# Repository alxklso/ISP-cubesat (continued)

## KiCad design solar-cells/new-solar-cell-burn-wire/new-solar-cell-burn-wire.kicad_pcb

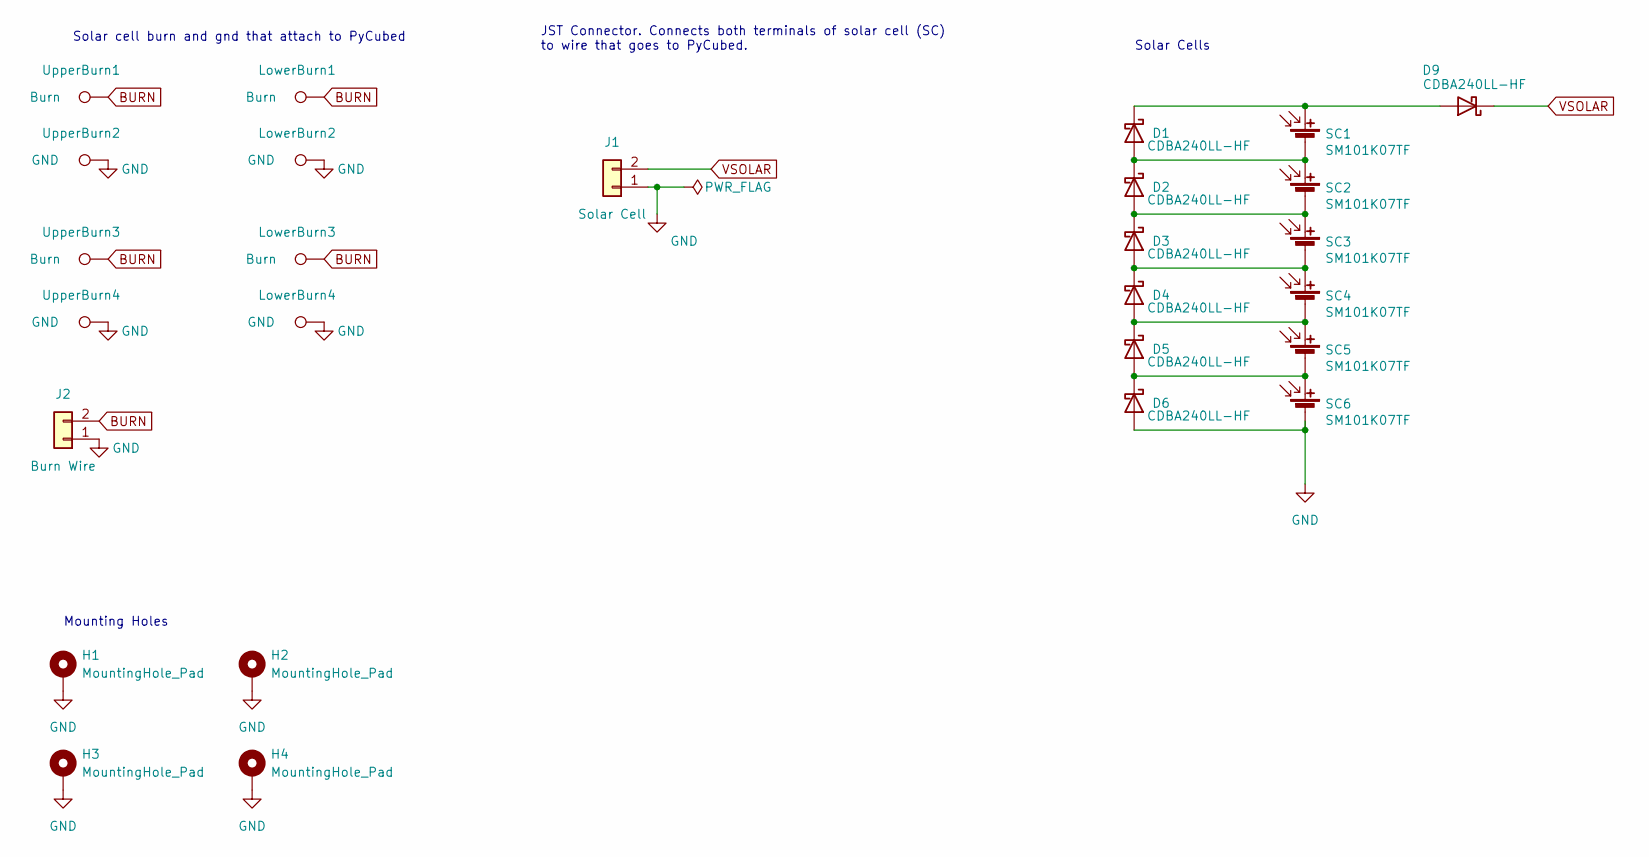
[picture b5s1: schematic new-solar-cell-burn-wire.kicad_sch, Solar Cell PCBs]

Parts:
D1, D2, D3, D4, D5, D6, D9: CDBA240LL-HF; DO-214AC
H1, H2, H3, H4: MountingHole_Pad; MountingHole_3.2mm_M3_DIN965_Pad
J1: Solar Cell; 2053380002
J2: Burn Wire; 2053380002
LowerBurn1, LowerBurn3: Burn; TestPoint_THTPad_2.0x2.0mm_Drill1.0mm
LowerBurn2, LowerBurn4: GND; TestPoint_THTPad_2.0x2.0mm_Drill1.0mm
SC1, SC2, SC3, SC4, SC5, SC6: SM101K07TF
UpperBurn1, UpperBurn3: Burn; TestPoint_THTPad_2.0x2.0mm_Drill1.0mm
UpperBurn2, UpperBurn4: GND; TestPoint_THTPad_2.0x2.0mm_Drill1.0mm

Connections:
BURN: J2.2, LowerBurn1.1, LowerBurn3.1, UpperBurn1.1, UpperBurn3.1
GND: D6.2 (A), H1.1, H2.1, H3.1, H4.1, J1.1, J2.1, LowerBurn2.1, LowerBurn4.1, SC6.2 (-), UpperBurn2.1, UpperBurn4.1; also elsewhere on the board
unnamed: D1.1 (K), D9.2 (A), SC1.1 (+)
unnamed: D1.2 (A), D2.1 (K), SC1.2 (-), SC2.1 (+)
unnamed: D2.2 (A), D3.1 (K), SC2.2 (-), SC3.1 (+)
unnamed: D3.2 (A), D4.1 (K), SC3.2 (-), SC4.1 (+)
unnamed: D4.2 (A), D5.1 (K), SC4.2 (-), SC5.1 (+)
unnamed: D5.2 (A), D6.1 (K), SC5.2 (-), SC6.1 (+)
VSOLAR: D9.1 (K), J1.2; also elsewhere on the board

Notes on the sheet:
Solar cell burn and gnd that attach to PyCubed
Mounting Holes
Solar Cells
JST Connector. Connects both terminals of solar cell (SC) to wire that goes to PyCubed.

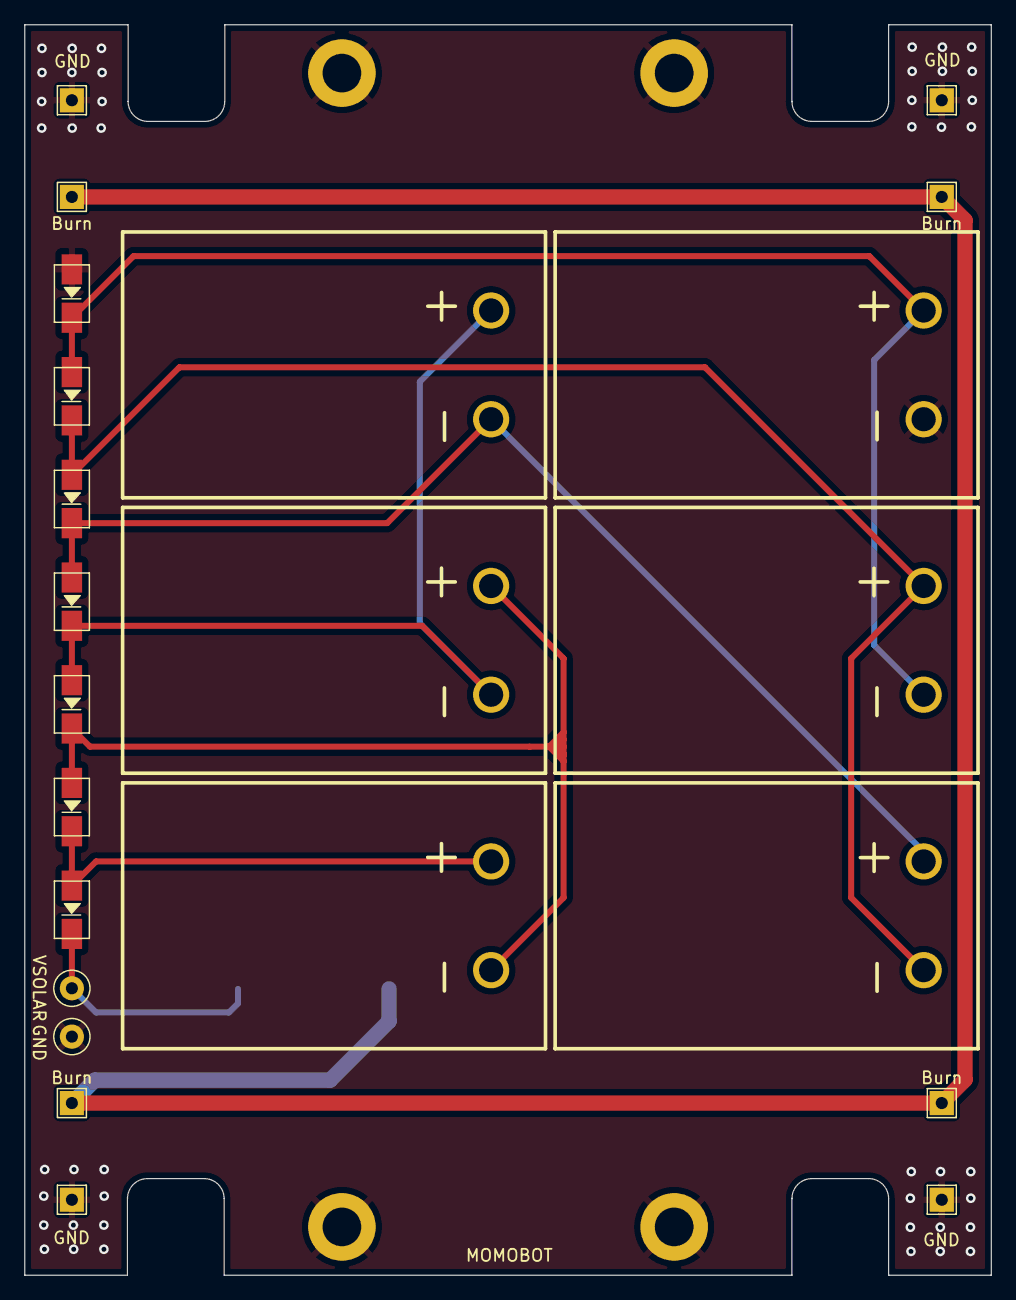
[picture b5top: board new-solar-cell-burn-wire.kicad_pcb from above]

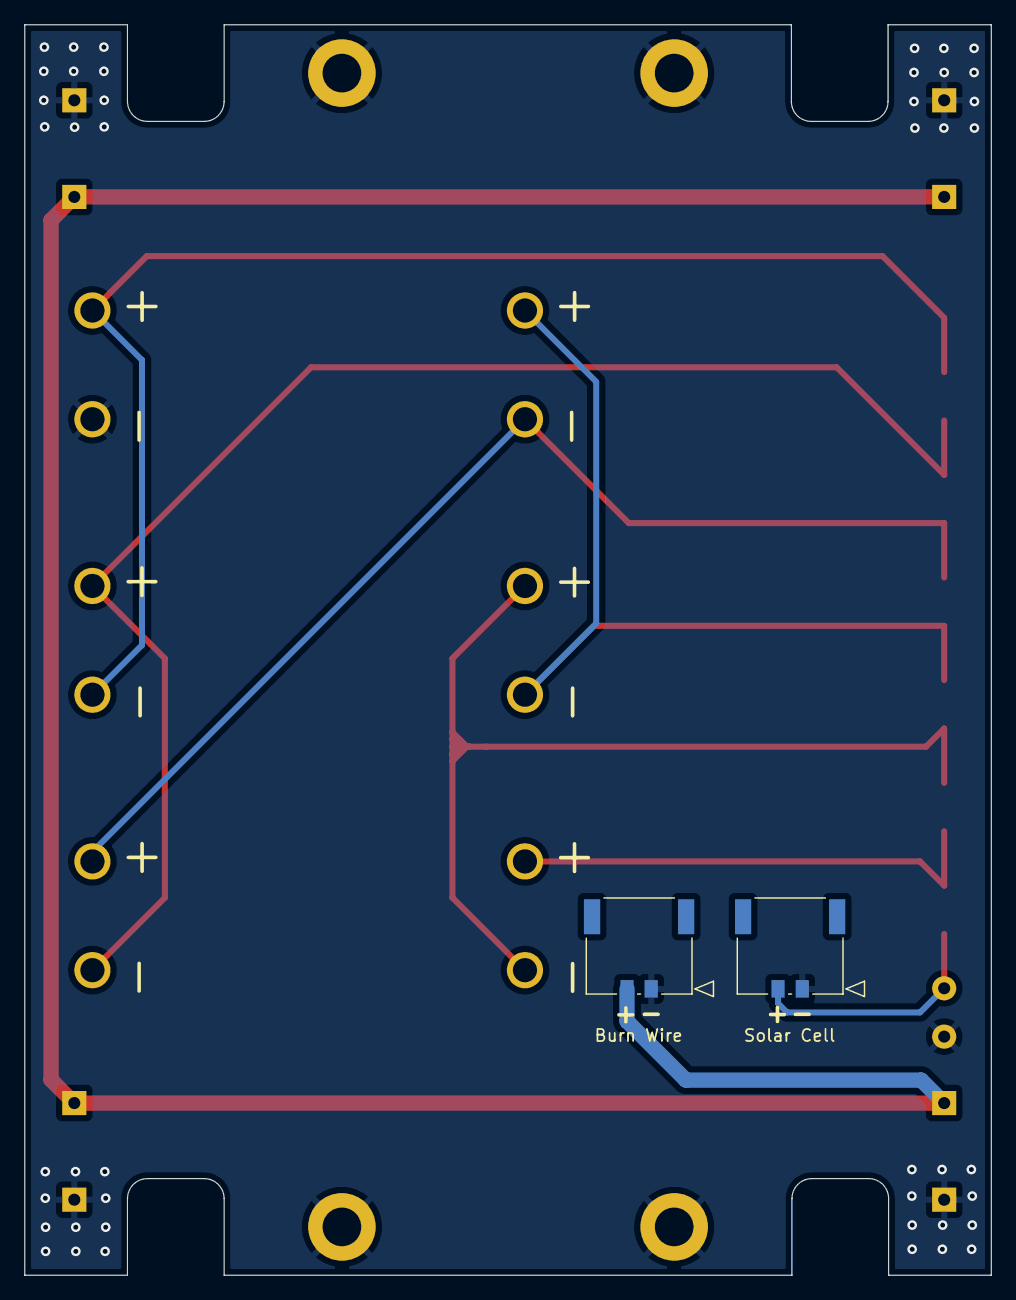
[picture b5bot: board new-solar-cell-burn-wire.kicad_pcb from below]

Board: 2 copper layers, 80.0 x 103.5 mm, 29 parts (2 on the bottom side), 9 nets.

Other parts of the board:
TP1: VSOLAR; TestPoint_Loop_D1.80mm_Drill1.0mm_Beaded
TP2: GND; TestPoint_Loop_D1.80mm_Drill1.0mm_Beaded

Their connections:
GND: TP2.1; also elsewhere on the board
VSOLAR: TP1.1; also elsewhere on the board
